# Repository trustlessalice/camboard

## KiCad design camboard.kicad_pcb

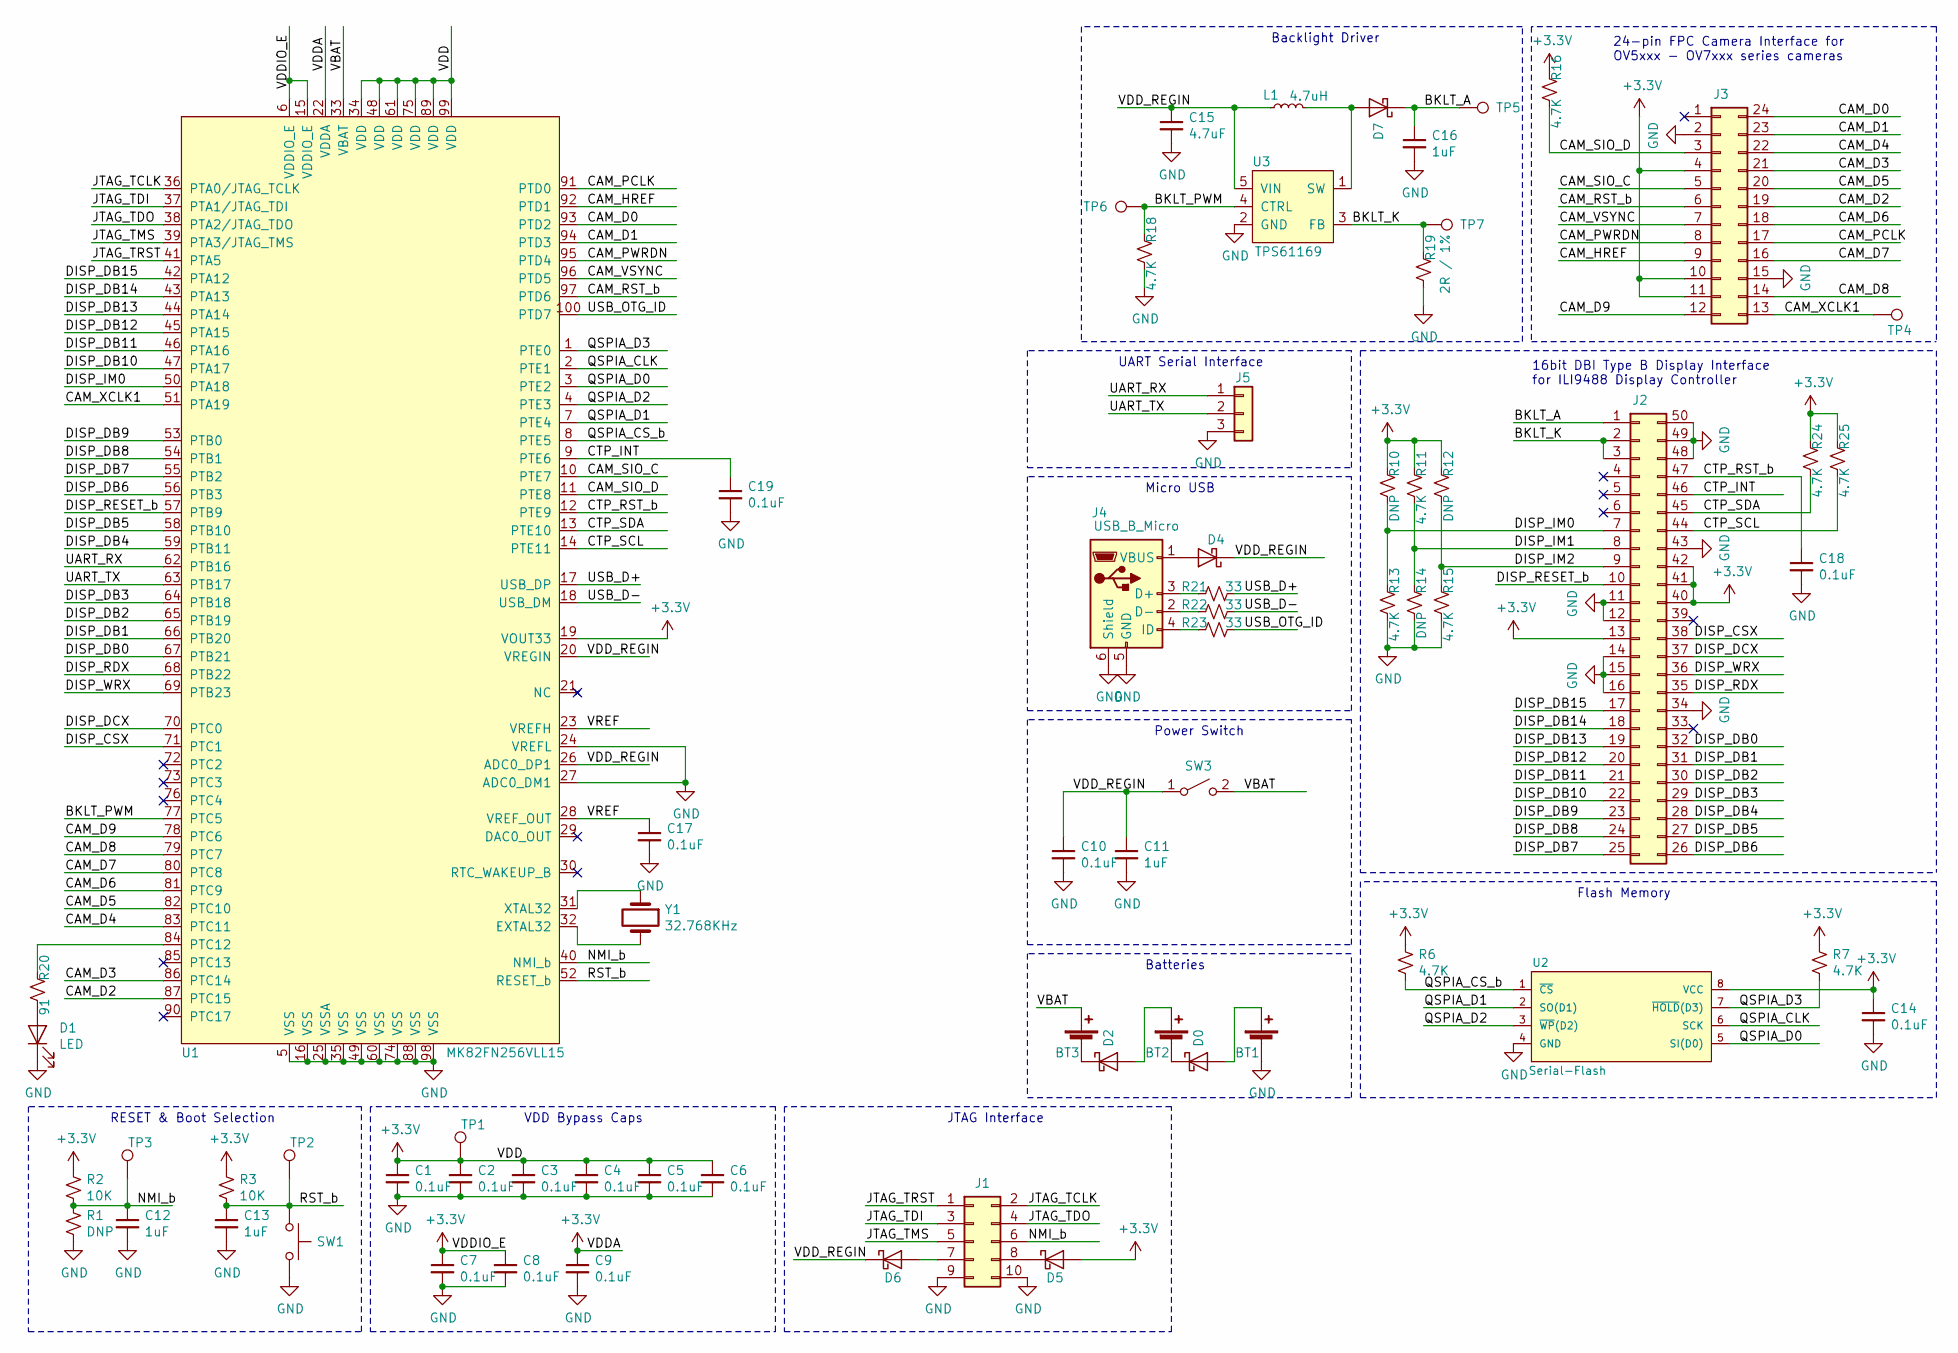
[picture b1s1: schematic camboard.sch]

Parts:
BT1, BT2, BT3: Battery_Cell; BAT_AAA_Keystone_55_56; MPN 55
C1, C2, C3, C4, C5, C6, C7, C8, C9, C10, C14, C17, C18, C19: 0.1uF; C_0402_1005Metric; MPN C0402C104K4RAC7411
C11, C12, C13: 1uF; C_0402_1005Metric; MPN C1005X5R1V105K050BE
C15: 4.7uF; C_0805_2012Metric; MPN 0805B475K6R3CT
C16: 1uF; C_0805_2012Metric
D0, D2, D4, D5, D6, D7: D_Schottky; D_SOT-23_ANK; MPN BAT54SHMFHT116
D1: LED; R_0603_1608Metric_Pad1.05x0.95mm_HandSolder; MPN SML-D12P8WT86C
J1: Conn_02x05_Odd_Even; PinHeader_2x05_P2.54mm_Vertical
J2: Conn_02x25_Counter_Clockwise; LCD_ER-TFT035-6; MPN 541045031
J3: Conn_02x12_Counter_Clockwise; OV5640-5MP-Camera; MPN 687124183722
J4: USB_B_Micro; USB_Micro-B_Molex_47346-0001; MPN 47346-0001
J5: Conn_01x03; PinHeader_1x03_P2.54mm_Vertical
L1: 4.7uH; L_0805_2012Metric_Pad1.15x1.40mm_HandSolder; MPN KLZ2012MHR4R7WTD25
R1, R10, R12, R14: DNP; R_0402_1005Metric
R2, R3: 10K; R_0402_1005Metric; MPN SFR01MZPF1002
R6, R7, R11, R13, R15, R16, R18, R24, R25: 4.7K; R_0402_1005Metric; MPN CRCW04024K70JNEDC
R19: 2R / 1%; R_0805_2012Metric_Pad1.15x1.40mm_HandSolder; MPN ERJ-6DQJ2R0V
R20: 91; R_0402_1005Metric; MPN ERJ-2RKF91R0X
R21, R22, R23: 33; R_0402_1005Metric; MPN CRCW040233R0JNEDC
SW1: SW_Push; TACTILE_SWITCH_SMD_6.0X3.5MM; MPN KSR251GLFS
SW3: SW_SPST; SWITCH_SPST_SMD_A; MPN PCM12SMTR
TP1, TP2, TP3, TP4, TP5, TP6, TP7: TestPoint; TestPoint_Pad_D1.5mm
U1: MK82FN256VLL15; MPN MK82FN256VLL15
U2: Serial-Flash; WSON8-6X5MM; MPN IS25WP016D-JKLE
U3: TPS61169; SC70-5; MPN TPS61169DCKR
Y1: 32.768KHz; Crystal_SMD_EuroQuartz_EQ161-2Pin_3.2x1.5mm; MPN ECS-.327-12.5-34B-TR

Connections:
+3V3: C1.1, C2.1, C3.1, C4.1, C5.1, C6.1, C7.1, C8.1, C9.1, C14.1, D5.2 (A), J2.13, J2.40, J2.41, J2.42, J3.4, J3.10, J3.11, R2.1, R3.1, R6.1, R7.1, R10.1, R11.1, R12.1, R16.1, R24.1, R25.1, TP1.1, U1.6 (VDDIO_E), U1.15 (VDDIO_E), U1.19 (VOUT33), U1.22 (VDDA), U1.34 (VDD), U1.48 (VDD), U1.61 (VDD), U1.75 (VDD), U1.89 (VDD), U1.99 (VDD), U2.8 (VCC)
/BKLT_A: C16.1, D7.1 (K), J2.1, TP5.1
/BKLT_K: J2.2, J2.3, R19.1, TP7.1, U3.3 (FB)
/BKLT_PWM: R18.1, TP6.1, U1.77 (PTC5), U3.4 (CTRL)
/CAM_D0: J3.24, U1.93 (PTD2)
/CAM_D1: J3.23, U1.94 (PTD3)
/CAM_D2: J3.19, U1.87 (PTC15)
/CAM_D3: J3.21, U1.86 (PTC14)
/CAM_D4: J3.22, U1.83 (PTC11)
/CAM_D5: J3.20, U1.82 (PTC10)
/CAM_D6: J3.18, U1.81 (PTC9)
/CAM_D7: J3.16, U1.80 (PTC8)
/CAM_D8: J3.14, U1.79 (PTC7)
/CAM_D9: J3.12, U1.78 (PTC6)
/CAM_HREF: J3.9, U1.92 (PTD1)
/CAM_PCLK: J3.17, U1.91 (PTD0)
/CAM_PWRDN: J3.8, U1.95 (PTD4)
/CAM_RST_b: J3.6, U1.97 (PTD6)
/CAM_SIO_C: J3.5, U1.10 (PTE7)
/CAM_SIO_D: J3.3, R16.2, U1.11 (PTE8)
/CAM_VSYNC: J3.7, U1.96 (PTD5)
/CAM_XCLK1: J3.13, TP4.1, U1.51 (PTA19)
/CTP_INT: C19.1, J2.46, U1.9 (PTE6)
/CTP_RST_b: C18.1, J2.47, U1.12 (PTE9)
/CTP_SCL: J2.44, R25.2, U1.14 (PTE11)
/CTP_SDA: J2.45, R24.2, U1.13 (PTE10)
/DISP_CSX: J2.38, U1.71 (PTC1)
/DISP_DB0: J2.32, U1.67 (PTB21)
/DISP_DB1: J2.31, U1.66 (PTB20)
/DISP_DB2: J2.30, U1.65 (PTB19)
/DISP_DB3: J2.29, U1.64 (PTB18)
/DISP_DB4: J2.28, U1.59 (PTB11)
/DISP_DB5: J2.27, U1.58 (PTB10)
/DISP_DB6: J2.26, U1.56 (PTB3)
/DISP_DB7: J2.25, U1.55 (PTB2)
/DISP_DB8: J2.24, U1.54 (PTB1)
/DISP_DB9: J2.23, U1.53 (PTB0)
/DISP_DB10: J2.22, U1.47 (PTA17)
/DISP_DB11: J2.21, U1.46 (PTA16)
/DISP_DB12: J2.20, U1.45 (PTA15)
/DISP_DB13: J2.19, U1.44 (PTA14)
/DISP_DB14: J2.18, U1.43 (PTA13)
/DISP_DB15: J2.17, U1.42 (PTA12)
/DISP_DCX: J2.37, U1.70 (PTC0)
/DISP_IM0: J2.7, R10.2, R13.1, U1.50 (PTA18)
/DISP_IM1: J2.8, R11.2, R14.1
/DISP_IM2: J2.9, R12.2, R15.1
/DISP_RDX: J2.35, U1.68 (PTB22)
/DISP_RESET_b: J2.10, U1.57 (PTB9)
/DISP_WRX: J2.36, U1.69 (PTB23)
/JTAG_TCLK: J1.2, U1.36 (PTA0/JTAG_TCLK)
/JTAG_TDI: J1.3, U1.37 (PTA1/JTAG_TDI)
/JTAG_TDO: J1.4, U1.38 (PTA2/JTAG_TDO)
/JTAG_TMS: J1.5, U1.39 (PTA3/JTAG_TMS)
/JTAG_TRST: J1.1, U1.41 (PTA5)
/NMI_b: C12.1, J1.6, R1.1, R2.2, TP3.1, U1.40 (NMI_b)
/QSPIA_CLK: U1.2 (PTE1), U2.6 (SCK)
/QSPIA_CS_b: R6.2, U1.8 (PTE5), U2.1 (~CS~)
/QSPIA_D0: U1.3 (PTE2), U2.5 (SI(D0))
/QSPIA_D1: U1.7 (PTE4), U2.2 (SO(D1))
/QSPIA_D2: U1.4 (PTE3), U2.3 (~WP~(D2))
/QSPIA_D3: R7.2, U1.1 (PTE0), U2.7 (~HOLD~(D3))
/RST_b: C13.1, R3.2, SW1.1, TP2.1, U1.52 (RESET_b)
/UART_RX: J5.1, U1.62 (PTB16)
/UART_TX: J5.2, U1.63 (PTB17)
/USB_D+: R21.2, U1.17 (USB_DP)
/USB_D-: R22.2, U1.18 (USB_DM)
/USB_OTG_ID: R23.2, U1.100 (PTD7)
/VBAT: BT3.1 (+), SW3.2 (B), U1.33 (VBAT)
/VDD_REGIN: C10.1, C11.1, C15.1, D4.1 (K), D6.1 (K), L1.1, SW3.1 (A), U1.20 (VREGIN), U1.26 (ADC0_DP1), U3.5 (VIN)
/VREF: C17.1, U1.23 (VREFH), U1.28 (VREF_OUT)
GND: BT1.2 (-), C1.2, C2.2, C3.2, C4.2, C5.2, C6.2, C7.2, C8.2, C9.2, C10.2, C11.2, C12.2, C13.2, C14.2, C15.2, C16.2, C17.2, C18.2, C19.2, D1.1 (K), J1.9, J1.10, J2.11, J2.12, J2.14, J2.15, J2.16, J2.34, J2.43, J2.48, J2.49, J2.50, J3.2, J3.15, J4.5 (GND), J4.6 (Shield), J5.3, R1.2, R13.2, R14.2, R15.2, R18.2, R19.2, SW1.2, U1.5 (VSS), U1.16 (VSS), U1.24 (VREFL), U1.25 (VSSA), U1.27 (ADC0_DM1), U1.35 (VSS), U1.49 (VSS), U1.60 (VSS), U1.74 (VSS), U1.88 (VSS), U1.98 (VSS), U2.4 (GND), U3.2 (GND)
unnamed: BT1.1 (+), D0.2 (A)
unnamed: BT2.1 (+), D2.2 (A)
unnamed: BT2.2 (-), D0.1 (K)
unnamed: BT3.2 (-), D2.1 (K)
unnamed: D1.2 (A), R20.2
unnamed: D4.2 (A), J4.1 (VBUS)
unnamed: D5.1 (K), J1.8
unnamed: D6.2 (A), J1.7
unnamed: D7.2 (A), L1.2, U3.1 (SW)
unnamed: J4.2 (D-), R22.1
unnamed: J4.3 (D+), R21.1
unnamed: J4.4 (ID), R23.1
unnamed: R20.1, U1.84 (PTC12)
unnamed: U1.31 (XTAL32), Y1.1
unnamed: U1.32 (EXTAL32), Y1.2

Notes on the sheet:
RESET & Boot Selection
VDD Bypass Caps
JTAG Interface
Flash Memory
16bit DBI Type B Display Interface for ILI9488 Display Controller
24-pin FPC Camera Interface for OV5xxx - OV7xxx series cameras
Backlight Driver
Batteries
Power Switch
Micro USB
UART Serial Interface

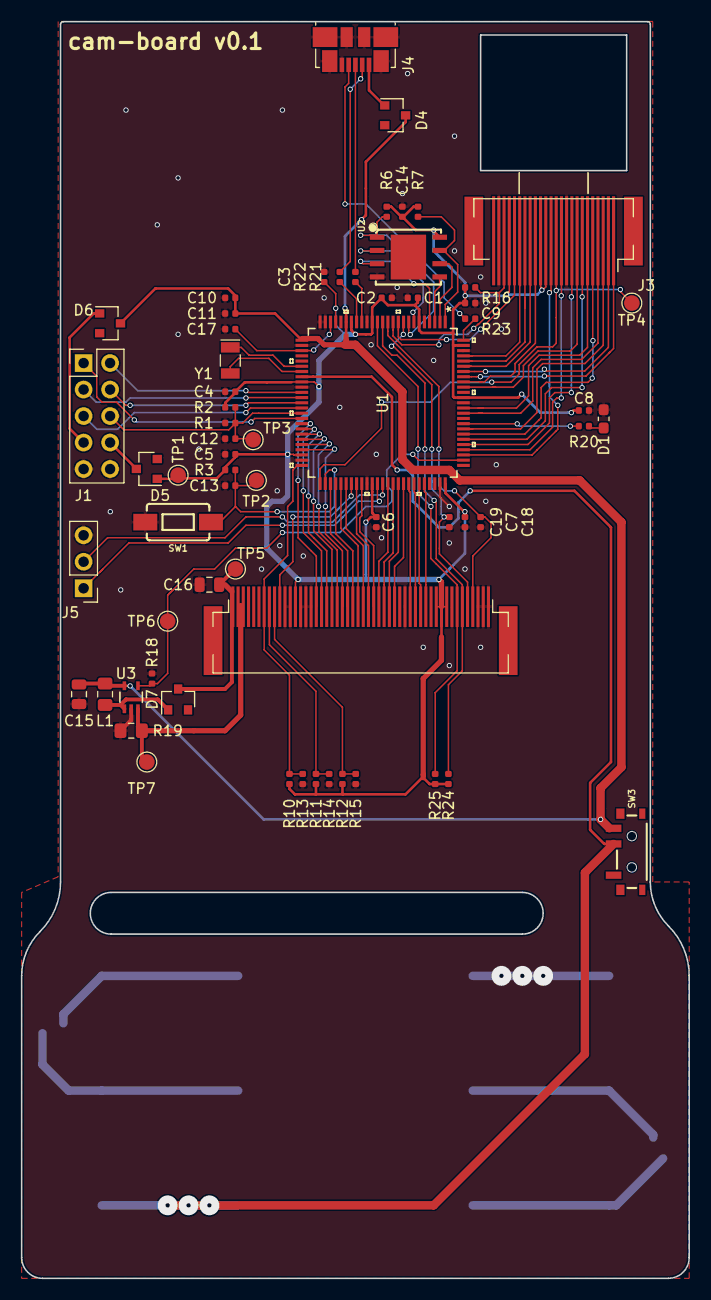
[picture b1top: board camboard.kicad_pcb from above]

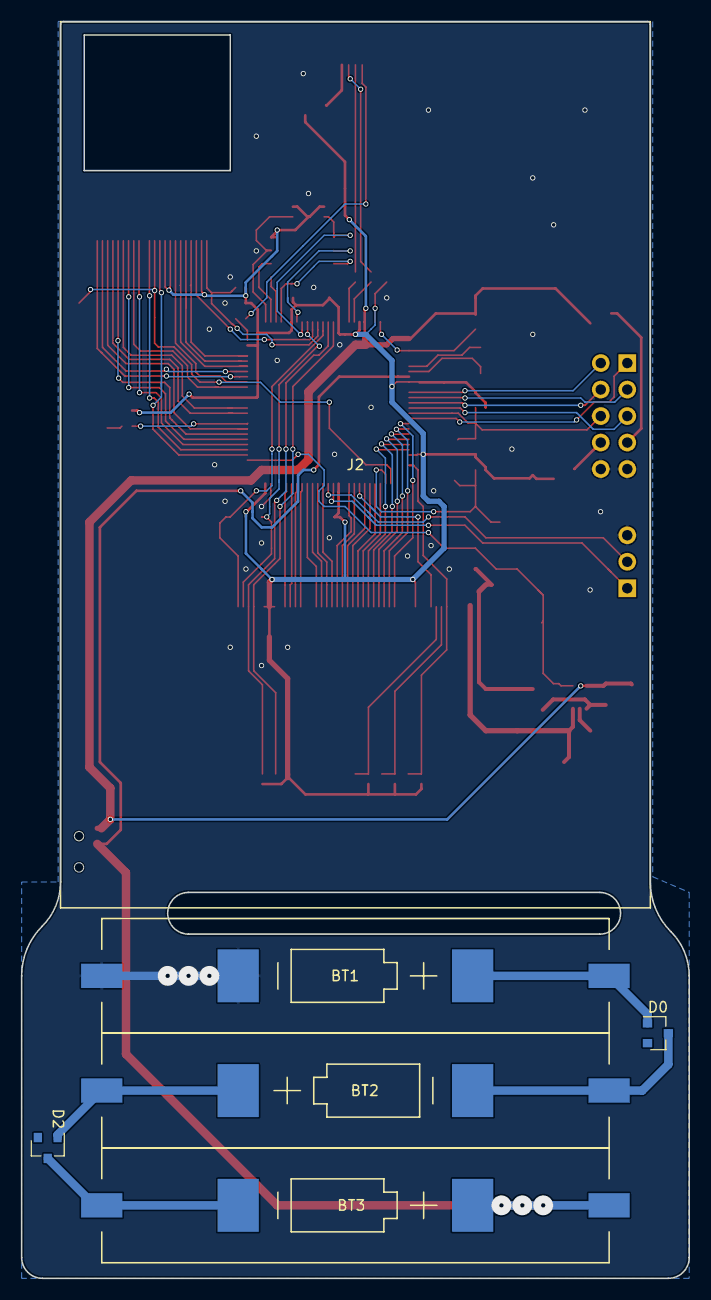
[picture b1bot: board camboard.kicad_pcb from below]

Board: 2 copper layers, 64.0 x 120.5 mm, 68 parts (5 on the bottom side), 87 nets.

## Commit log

2019-02-21 Kinetis MK82 template schematic
2019-02-23 Add FPC connector for display
2019-03-02 Schematic capture complete
2019-03-03 Add serial port and USB connectors
2019-03-20 Layout complete
2019-03-30 Update switch MPN
2019-03-30 Update 4.7uF MPN
2019-03-31 Update MPN for reset button
2019-03-31 Power LCD backlight from VREG_IN, instead of 3.3 rail
2019-03-31 Ignore fp-info-cache

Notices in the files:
parts and their libraries:
Copyright 2016 Accelerated Designs. All rights reserved.
